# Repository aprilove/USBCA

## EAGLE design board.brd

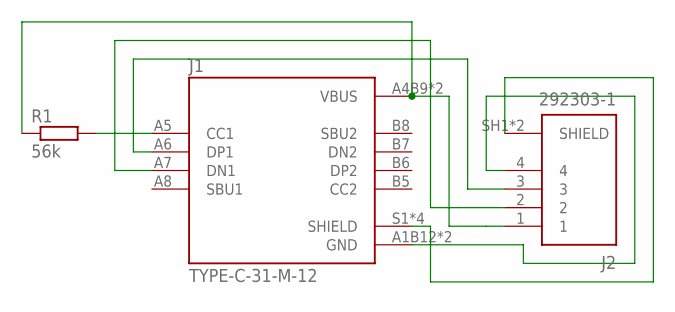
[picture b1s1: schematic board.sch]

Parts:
J1: TYPE-C-31-M-12; HRO_TYPE-C-31-M-12
J2: 292303-1
R1: 56k; R0603

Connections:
unnamed: J1.A1B12 (GND), J1.B1A12 (GND), J2.4
unnamed: J1.S1 (SHIELD), J1.S2 (SHIELD), J1.S3 (SHIELD), J1.S4 (SHIELD), J2.SH1 (SHIELD), J2.SH2 (SHIELD)
unnamed: J1.A4B9 (VBUS), J1.B4A9 (VBUS), J2.1, R1.1
unnamed: J1.A6 (DP1), J2.3
unnamed: J1.A7 (DN1), J2.2
unnamed: J1.A5 (CC1), R1.2

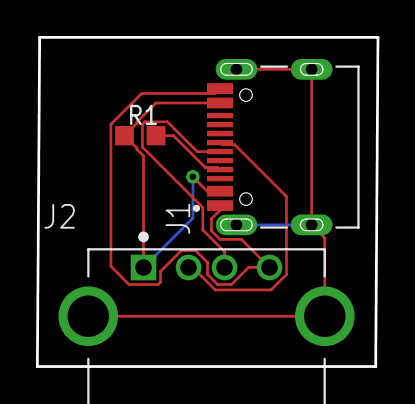
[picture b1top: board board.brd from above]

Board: 2 copper layers, 18.9 x 18.3 mm, 3 parts (0 on the bottom side), 6 nets.
